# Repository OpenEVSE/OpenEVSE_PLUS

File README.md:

# OpenEVSE_PLUS
README.md for OpenEVSE Hardware
Files SCH and BRD in Eagle format
License CC BY-SA 3.0
OpenEVSE Hardware

Current Version OpenEVSE_PLUS_v6.5.1.

OpenEVSE_PLUS_V6.5 - New more powerfull 10 watt Power supply (v5.5 and below 4 watt) with support for 277V AC and higher 85C operational temperature. Reworked AC detect circuits to support new UL requirement for "Continuous" Ground Monitoring vs "While Charging". Pulled ADC6 HIGH to auto detect CGMI requirement. Added on-board Surge supression MOVs. Added connector with Pilot, Proximity Pilot, Ground and 5v.

OpenEVSE_PLUS_V5.5 - Moved GFCI Test pin to enable move of DC Relay outputs to PWM capable pins supporting full power closing reduced power holding in OpenEVSE 7.1.2+ firmware. Pulled PD7 HIGH to auto detect board version in software to automatically set new/old pin values without requiring different firmware. Replaced 0.1" generic non-polarized connectors with JST PH for Serial (WiFi) and i2c (Display). Combined power and data connections for WiFi to reduce eliminate a screw terminal connector and simplify wiring harness. Replaced DC/DC converter with a TC1044S invert chip to generate -12v from +12v. 

OpenEVSE_PLUS_v5 - Optimized for reduced build time and high volume manufacturing of changing stations, removed most screw terminals and replaced with common connectors. Change from 2 single chanel opto-isolators for AC detection to 1 dual channel. Added ground connections to screw holes.

OpenEVSE_PLUS_v4 - Has 2 AC Detect chips like v1 + v2 plus the AC relay driver of v3. Added rectifier diodes to AC detect to improve detection in some conditions. Changed GFCI to individual pinout 4 pins.

OpenEVSE_PLUS_v3 - Removed 1 AC Detect chip and added AC relay driver. Added Current measurement circuit

OpenEVSE_PLUS_v2.5 - Added Current measurement circuit.

OpenEVSE_PLUS_v2 - modified GFCI pinout

OpenEVSE_PLUS_v1 - Inital version - Combined OpenEVSE v7 board and Advanced power supply into single board

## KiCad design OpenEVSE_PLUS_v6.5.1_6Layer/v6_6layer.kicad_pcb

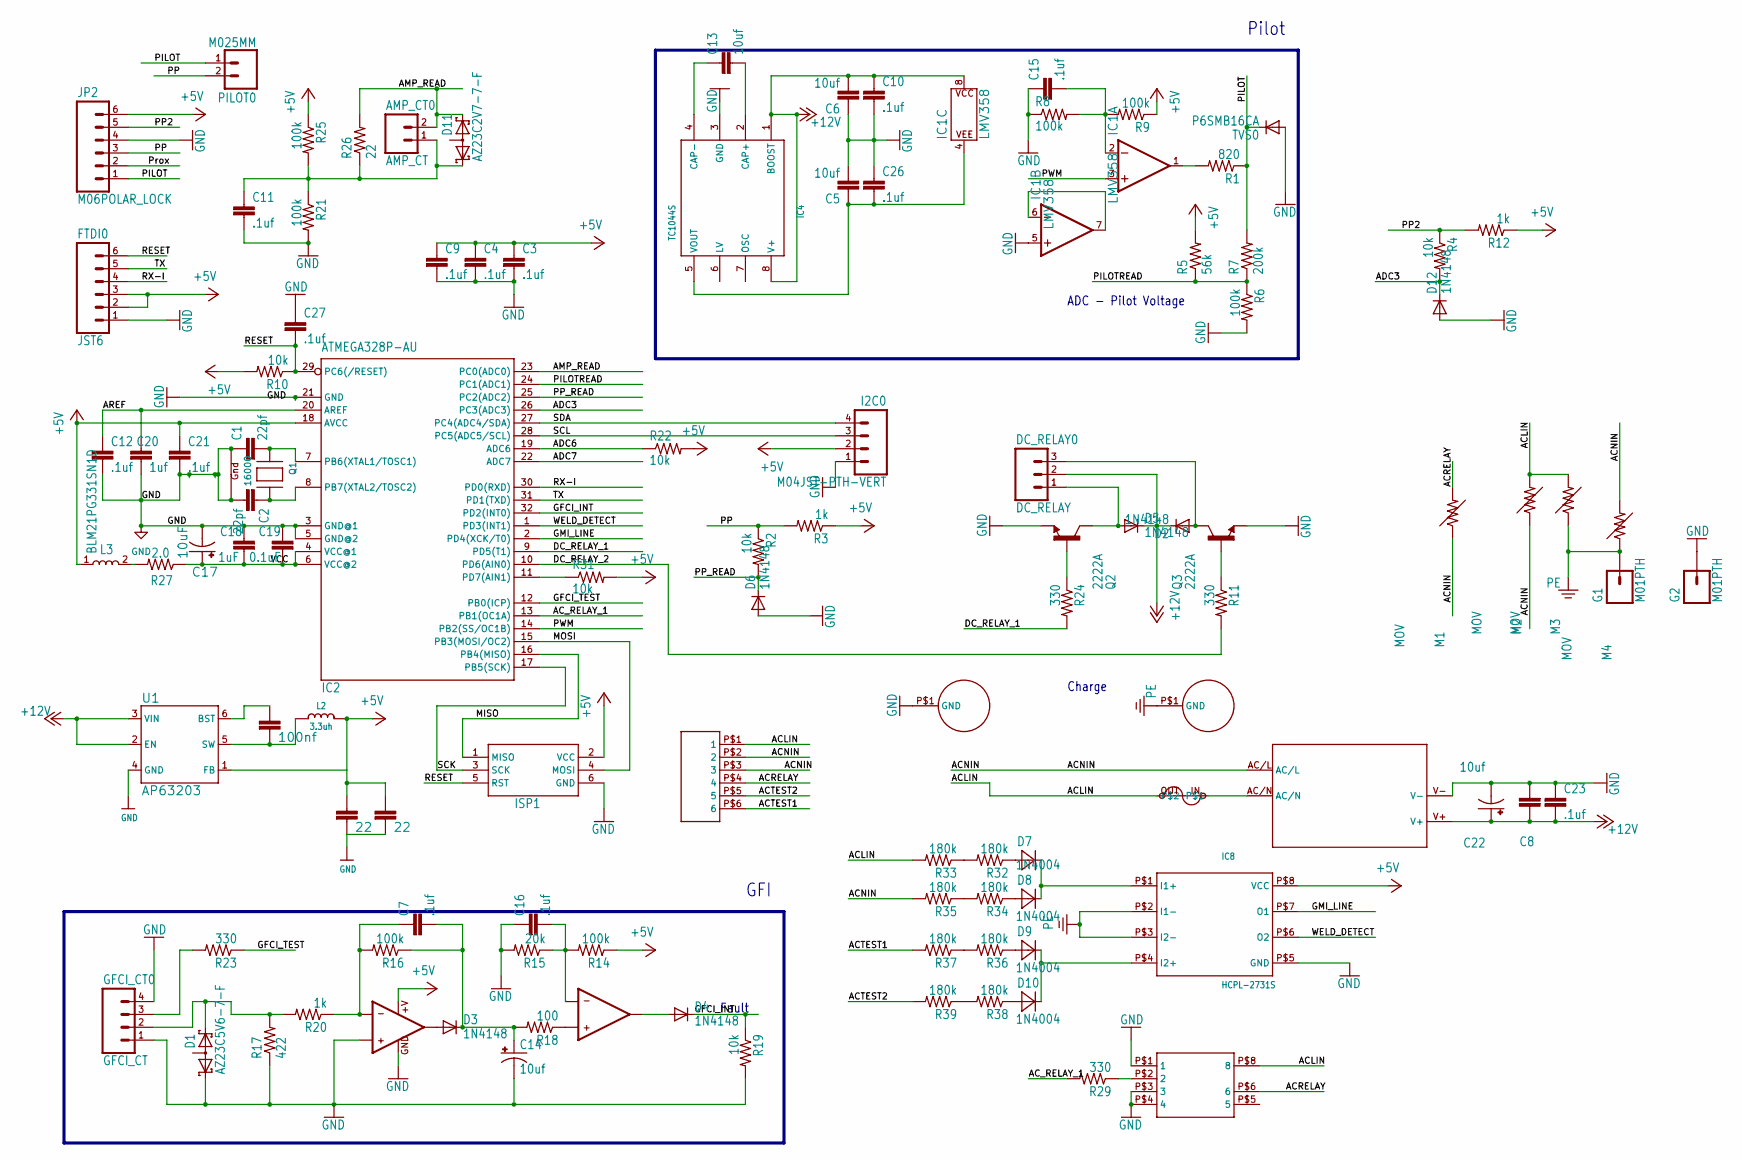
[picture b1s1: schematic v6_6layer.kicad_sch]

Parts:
AC0: JST-VH-6
AMP_CT0: AMP_CT; MOLEX_2
C1, C2: 22pf; 0805
C3, C4, C7, C9, C10, C11, C12, C15, C16, C21, C23, C26, C27: .1uf; 0805
C5, C6, C13: 10uf; 0805
C8, C20: 1uf; 0805
C14, C22: 10uf; EIA3216
C17: 10uF; 0603-POLAR
C18: 1uF; 0805
C19: 0.1uF; 0805
C29, C33: 22; 0805
C32: 100nf; 0805
D1: AZ23C5V6-7-F; SOT23
D2, D3, D4, D5, D6, D12: 1N4148; SOD123
D7, D8, D9, D10: 1N4004; SMA
D11: AZ23C2V7-7-F; SOT23
DC_RELAY0: DC_RELAY; MOLEX_3
F1: BEL1.6AFUSE; BELFUSE1A
FTDI0: JST6
G1, G2: M01PTH; 1X01
GFCI_CT0: GFCI_CT; GFCI_4
I2C0: M04JST-PTH-VERT; JST-4-PTH-VERT
IC1: LMV358; SO08
IC2: ATMEGA328P-AU; TQFP32-08
IC3: LM358; SO08
IC4: TC1044S; SO-8
IC7: AQH2223; SIL8
IC8: HCPL-2731S; SIL8-2
ISP1: ISP1; AVRISP
JP2: M06POLAR_LOCK; MOLEX-1X6_LOCK
L2: 3.3uh; MICROBUILDER_INDUCTOR_5X5MM_NR5040_NOTHERMALS
L3: BLM21PG331SN1D; INDC2012X87
M1, M2, M3, M4: MOV
PILOT0: M025MM; SCREWTERMINAL-5MM-2
PS1: IRM-10-5
Q1: 16000; NX3225
Q2, Q3: 2222A; SOT23
R1: 820; 0805
R2, R4, R10, R19, R22, R31: 10k; 0805
R3, R12, R20: 1k; 0805
R5: 56k; 0805
R6, R8, R9, R14, R16, R21, R25: 100k; 0805
R7: 200k; 0805
R11, R23, R24, R29: 330; 0805
R15: 20k; 0805
R17: 422; 0805
R18: 100; 0805
R26: 22; R1206
R27: 2.0; 0805
R32, R33, R34, R35, R36, R37, R38, R39: 180k; 1210
TVS0: P6SMB16CA; SMB
U1: AP63203; SOT23-6
U$3, U$9: HOLE

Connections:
+5V: C3.1, C4.1, C9.1, C21.1, C29.1, C33.1, FTDI0.2, FTDI0.3, I2C0.2, IC2.18 (AVCC), IC3.8 (+V), IC8.P$8 (VCC), ISP1.2 (VCC), JP2.6, L2.P$2 (2), L3.1, R3.1, R5.2, R9.1, R10.2, R12.1, R14.1, R22.2, R25.1, R31.2, U1.1 (FB); also elsewhere on the board
+12V: C6.2, C8.1, C10.1, C22.A (+), C23.2, D2.C, D5.C, DC_RELAY0.2, IC1.8 (P$V+), IC4.1 (BOOST), IC4.8 (V+), PS1.V+, U1.2 (EN), U1.3 (VIN); also elsewhere on the board
-12V1: C5.1, C26.2, IC1.4 (P$V-), IC4.5 (VOUT)
ACLIN: AC0.P$1 (1), F1.OUT, IC7.P$8 (8), M2.P$2 (2), M3.P$2 (2), R33.2
ACNIN: AC0.P$2 (2), AC0.P$3 (3), M1.P$1 (1), M2.P$1 (1), M4.P$2 (2), PS1.AC/L, R35.2
ACRELAY: AC0.P$4 (4), IC7.P$6 (6), M1.P$2 (2)
ACTEST1: AC0.P$6 (6), R37.2
ACTEST2: AC0.P$5 (5), R39.2
AC_RELAY_1: IC2.13 (PB1(OC1A)), R29.2
ADC3: D12.C, IC2.26 (PC3(ADC3)), R4.2
ADC6: IC2.19 (ADC6), R22.1
ADC7: IC2.22 (ADC7)
AMP_READ: AMP_CT0.2, D11.2 (K2), IC2.23 (PC0(ADC0)), R26.2
AREF: C12.1, C20.1, IC2.20 (AREF)
DAMP: L3.2, R27.2
DC_RELAY_1: IC2.9 (PD5(T1)), R24.2
DC_RELAY_1_O: D5.A, DC_RELAY0.1, Q2.3 (C); also elsewhere on the board
DC_RELAY_1_T: Q2.1 (B), R24.1
DC_RELAY_2: IC2.10 (PD6(AIN0)), R11.2
DC_RELAY_2_O: D2.A, DC_RELAY0.3, Q3.3 (C); also elsewhere on the board
DC_RELAY_2_T: Q3.1 (B), R11.1
GFCI_INT: D4.C, IC2.32 (PD2(INT0)), R19.1
GFCI_TEST: IC2.12 (PB0(ICP)), R23.1
GFI_TEST_O: GFCI_CT0.3, R23.2; also elsewhere on the board
GMI_LINE: IC2.2 (PD4(XCK/T0)), IC8.P$7 (O1)
GND: C1.1, C2.2, C3.2, C4.2, C5.2, C6.1, C8.2, C9.2, C10.2, C11.2, C12.2, C14.C (-), C15.1, C16.1, C17.-, C18.1, C19.1, C20.2, C21.2, C22.C (-), C23.1, C26.1, C27.1, C29.2, C33.2, D1.1 (K1), D6.A, D12.A, FTDI0.1, G2.1, GFCI_CT0.1, GFCI_CT0.4, I2C0.1, IC1.5 (+IN), IC2.3 (GND@1), IC2.5 (GND@2), IC2.21 (GND), IC3.3 (+IN1), IC3.4 (GND), IC4.3 (GND), IC7.P$1 (1), IC7.P$3 (3), IC7.P$4 (4), IC8.P$5 (GND), ISP1.6 (GND), JP2.4, PS1.V-, Q1.1 (G1), Q1.3 (G2), Q2.2 (E), Q3.2 (E), R6.2, R8.1, R15.2, R17.1, R19.2, R21.2, TVS0.A, U1.4 (GND), U$9.P$1; also elsewhere on the board
MISO: IC2.16 (PB4(MISO)), ISP1.1 (MISO)
MOSI: IC2.15 (PB3(MOSI/OC2)), ISP1.4 (MOSI)
unnamed: D9.C, D10.C, IC8.P$4 (I2+)
unnamed: D7.C, D8.C, IC8.P$1 (I1+)
unnamed: C1.2, IC2.7 (PB6(XTAL1/TOSC1)), Q1.2 (X1)
unnamed: C2.1, IC2.8 (PB7(XTAL2/TOSC2)), Q1.4 (X2)
unnamed: D7.A, R32.1
unnamed: AMP_CT0.1, C11.1, D11.1 (K1), R21.1, R25.2, R26.1
unnamed: C7.1, IC3.2 (-IN1), R16.2, R20.1
unnamed: D8.A, R34.1
unnamed: C15.2, IC1.2 (-IN), R8.2, R9.2
unnamed: IC1.1 (OUT), R1.2
unnamed: IC2.11 (PD7(AIN1)), R31.1
unnamed: R32.2, R33.1
unnamed: IC1.6 (-IN), IC1.7 (OUT)
unnamed: C32.1, U1.6 (BST)
unnamed: C32.2, L2.P$1 (1), U1.5 (SW)
unnamed: R34.2, R35.1
unnamed: IC7.P$2 (2), R29.1
unnamed: C13.2, IC4.2 (CAP+)
unnamed 46: D1.2 (K2), GFCI_CT0.2, R17.2, R20.2; also elsewhere on the board
unnamed: D3.A, IC3.1 (OUT1)
unnamed: R36.2, R37.1
unnamed: C7.2, C14.A (+), D3.C, R16.1, R18.2
unnamed: C16.2, IC3.6 (-IN2), R14.2, R15.1
unnamed: D4.A, IC3.7 (OUT2)
unnamed: IC3.5 (+IN2), R18.1
unnamed: C13.1, IC4.4 (CAP-)
unnamed: R38.2, R39.1
unnamed: D9.A, R36.1
unnamed: D10.A, R38.1
unnamed: F1.IN, PS1.AC/N
PE: G1.1, IC8.P$2 (I1-), IC8.P$3 (I2-), M3.P$1 (1), M4.P$1 (1), U$3.P$1
PILOT: JP2.1, PILOT0.1, R1.1, R7.2, TVS0.C; also elsewhere on the board
PILOTREAD: IC2.24 (PC1(ADC1)), R5.1, R6.1, R7.1
PP: JP2.3, PILOT0.2, R2.1, R3.2; also elsewhere on the board
PP2: JP2.5, R4.1, R12.2
PP_READ: D6.C, IC2.25 (PC2(ADC2)), R2.2
PWM: IC1.3 (+IN), IC2.14 (PB2(SS/OC1B))
RESET: C27.2, FTDI0.6, IC2.29 (PC6(/RESET)), ISP1.5 (RST), R10.1; also elsewhere on the board
RX-I: FTDI0.4, IC2.30 (PD0(RXD)); also elsewhere on the board
SCK: IC2.17 (PB5(SCK)), ISP1.3 (SCK)
SCL: I2C0.3, IC2.28 (PC5(ADC5/SCL)); also elsewhere on the board
SDA: I2C0.4, IC2.27 (PC4(ADC4/SDA)); also elsewhere on the board
TX: FTDI0.5, IC2.31 (PD1(TXD)); also elsewhere on the board
VCC: C17.+, C18.2, C19.2, IC2.4 (VCC@1), IC2.6 (VCC@2), R27.1
WELD_DETECT: IC2.1 (PD3(INT1)), IC8.P$6 (O2)

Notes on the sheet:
Fault
Charge
GFI
ADC - Pilot Voltage
Pilot

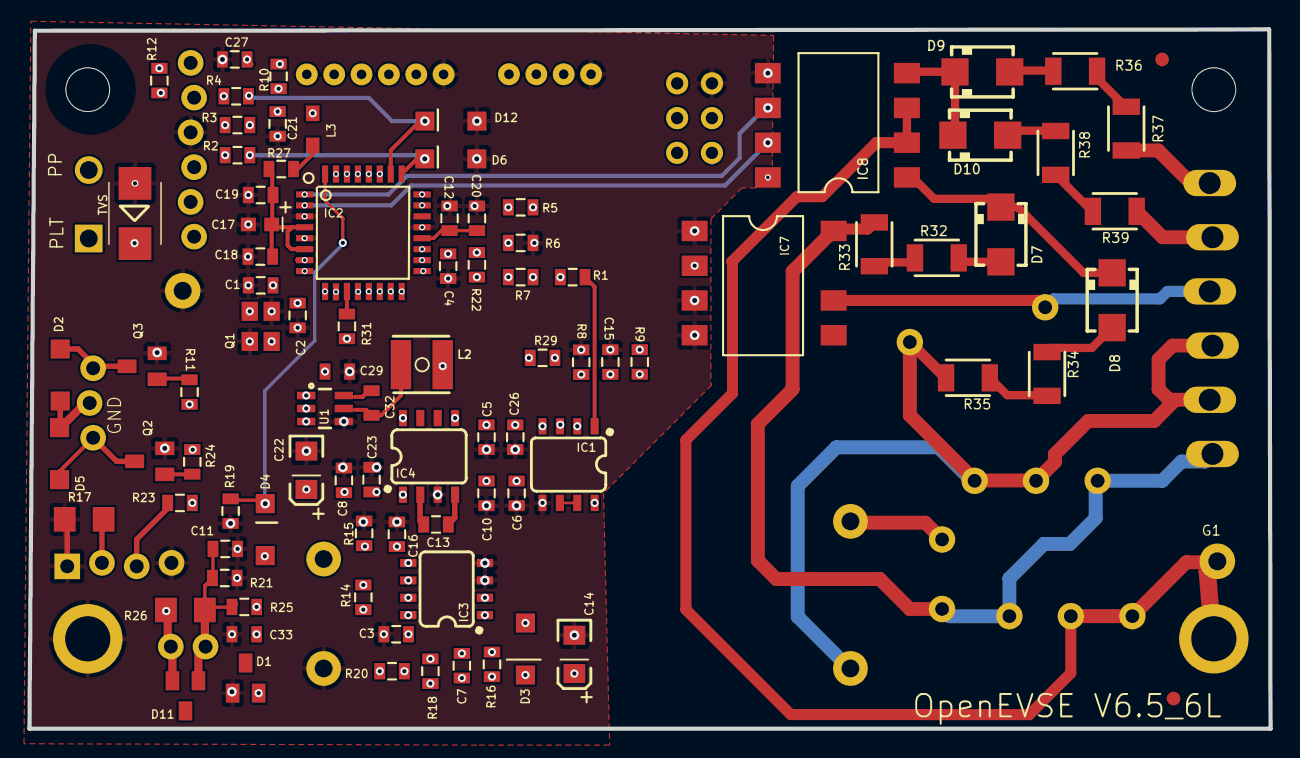
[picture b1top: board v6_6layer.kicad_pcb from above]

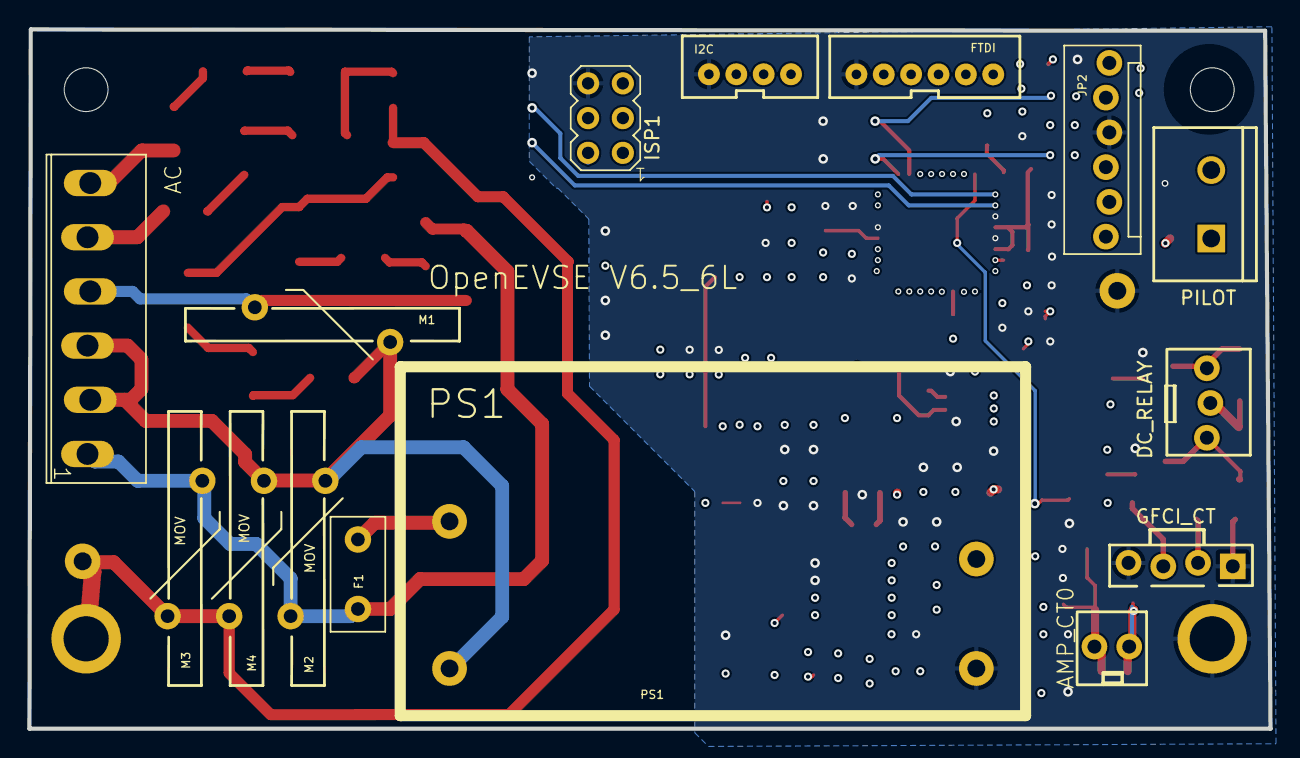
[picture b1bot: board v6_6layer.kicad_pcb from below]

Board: 6 copper layers, 90.7 x 51.1 mm, 111 parts (15 on the bottom side), 72 nets.

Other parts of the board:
@HOLE0, @HOLE1: (no value)
DC_RELAY: DC_RELAY; MOLEX_3
FID1, FID3: FIDUCIAL1X2.5; FIDUCIAL-1X2.5
FTDI: JST6
GFCI_CT: GFCI_CT; GFCI_4
I2C: JST-4-PTH-VERT
PILOT: SCREWTERMINAL-5MM-2
TVS: P6SMB16CA; SMB

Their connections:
+5V: FTDI.2, FTDI.3, I2C.2; also elsewhere on the board
+12V: DC_RELAY.2; also elsewhere on the board
DC_RELAY_1_O: DC_RELAY.1; also elsewhere on the board
DC_RELAY_2_O: DC_RELAY.3; also elsewhere on the board
GFI_TEST_O: GFCI_CT.3; also elsewhere on the board
GND: FTDI.1, GFCI_CT.1, GFCI_CT.4, I2C.1, TVS.A; also elsewhere on the board
unnamed 46: GFCI_CT.2; also elsewhere on the board
PILOT: PILOT.1, TVS.C; also elsewhere on the board
PP: PILOT.2; also elsewhere on the board
RESET: FTDI.6; also elsewhere on the board
RX-I: FTDI.4; also elsewhere on the board
SCL: I2C.3; also elsewhere on the board
SDA: I2C.4; also elsewhere on the board
TX: FTDI.5; also elsewhere on the board

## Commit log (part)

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2025-03-10 Upload OpenEVSE v 6.5.1
2025-03-10 Update README.md
    Added v6.5
2026-05-26 Revise README for OpenEVSE_PLUS_V6.5 and V5.5 updates
    Updated the README to reflect changes in OpenEVSE_PLUS_V6.5 and V5.5, including new features and improvements.
